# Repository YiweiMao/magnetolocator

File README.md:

# magnetolocator

Check here to see our progress:
Hackathon Force Feedback VR Glove
https://docs.google.com/document/d/1uaAP13nhqvj-tF6IxJNAysReoOo3x5oB9gJD-OO6OQ0/edit

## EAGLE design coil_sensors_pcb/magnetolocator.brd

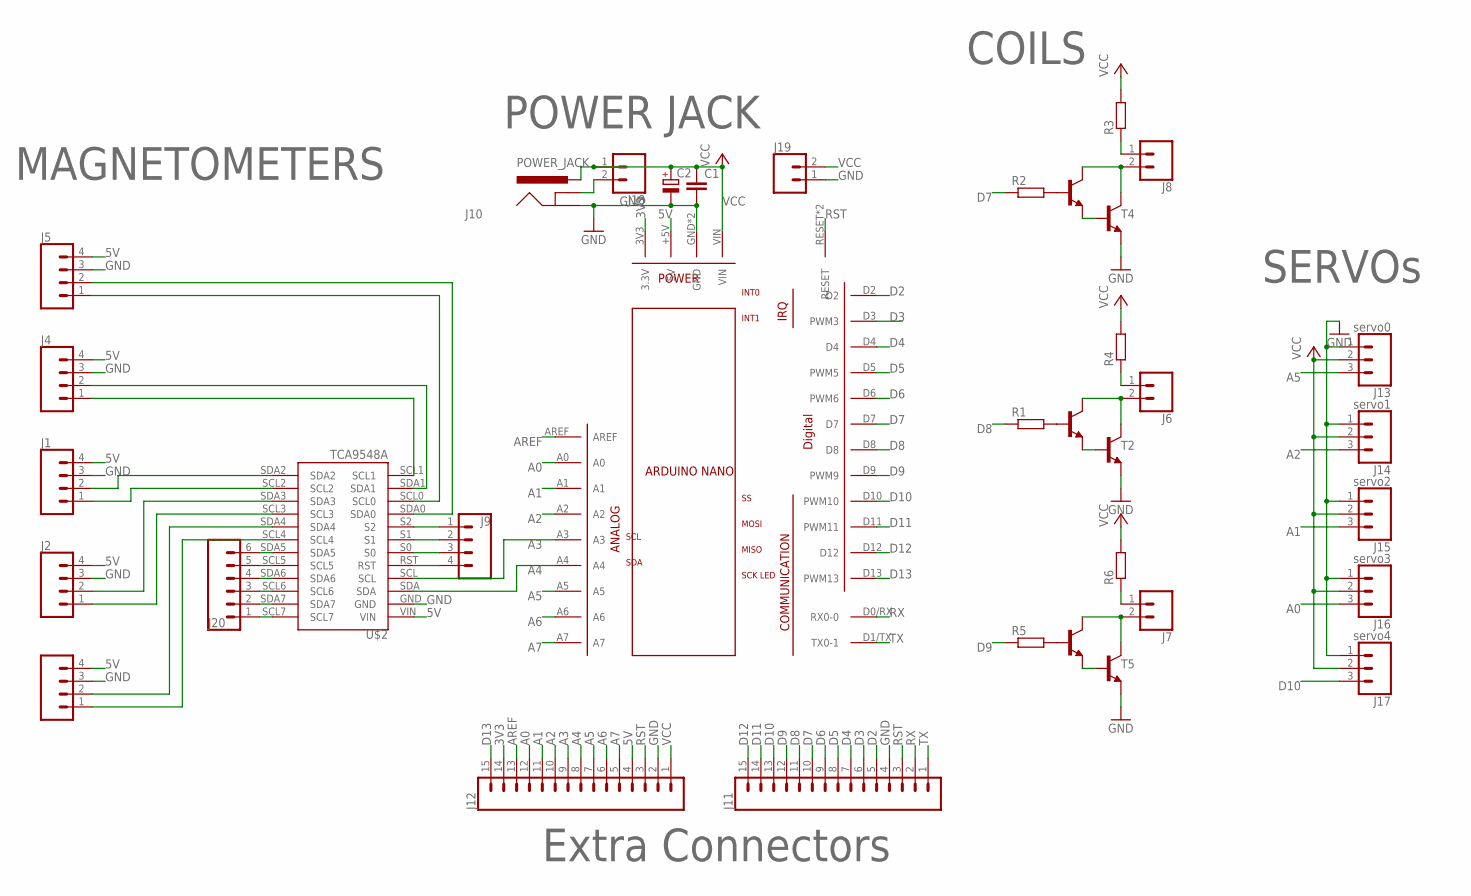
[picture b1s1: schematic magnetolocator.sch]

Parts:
C1: C-EU025-025X050; C025-025X050
C2: CPOL-EUE2.5-5; E2,5-5
J1, J2, J3, J4, J5, J9: CONN_04PTH; 1X04
J6, J7, J8, J18, J19: CONN_02; 1X02
J10: POWER_JACK; POWER_JACK_PTH
J11, J12: CONN_15; 1X15
J13: servo0; 1X03
J14: servo1; 1X03
J15: servo2; 1X03
J16: servo3; 1X03
J17: servo4; 1X03
J20: CONN_06NO_SILK_FEMALE_PTH; 1X06_NO_SILK
R1, R2, R3, R4, R5, R6: R-EU_0207/2V; 0207/2V
T1, T2, T3, T4, T5, T6: 2N2222-NPN-TO92-EBC; TO92-EBC
U$1: BOARD_ARDUINO-NANO; BOARD_ARDUINO_NANO
U$2: TCA9548A

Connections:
3V3: J12.14, U$1.3V3 (3.3V)
5V: J1.4, J2.4, J3.4, J4.4, J5.4, J12.4, U$1.+5V (5V), U$2.VIN
A0: J12.12, J16.3, U$1.A0
A1: J12.11, J15.3, U$1.A1
A2: J12.10, J14.3, U$1.A2
A3: J12.9, U$1.A3, U$2.SCL
A4: J12.8, U$1.A4, U$2.SDA
A5: J12.7, J13.3, U$1.A5
A6: J12.6, U$1.A6
A7: J12.5, U$1.A7
AREF: J12.13, U$1.AREF
D2: J11.5, U$1.D2
D3: J11.6, U$1.D3 (PWM3)
D4: J11.7, U$1.D4
D5: J11.8, U$1.D5 (PWM5)
D6: J11.9, U$1.D6 (PWM6)
D7: J11.10, R2.1, U$1.D7
D8: J11.11, R1.1, U$1.D8
D9: J11.12, R5.1, U$1.D9 (PWM9)
D10: J11.13, J17.3, U$1.D10 (PWM10)
D11: J11.14, U$1.D11 (PWM11)
D12: J11.15, U$1.D12
D13: J12.15, U$1.D13 (PWM13)
GND: C1.2, C2.-, J1.3, J2.3, J3.3, J4.3, J5.3, J10.GND, J11.4, J12.2, J13.1, J14.1, J15.1, J16.1, J17.1, J19.1, T2.E, T4.E, T5.E, U$1.GND, U$1.GND1 (GND), U$2.GND
unnamed: R2.2, T1.B
unnamed: R1.2, T3.B
unnamed: J3.1, U$2.SCL4
unnamed: J3.2, U$2.SDA4
unnamed: J8.1, R3.1
unnamed: J10.GNDBREAK, J18.2
unnamed: T1.E, T4.B
unnamed: J8.2, T1.C, T4.C
unnamed: J2.1, U$2.SCL3
unnamed: J2.2, U$2.SDA3
unnamed: J6.1, R4.1
unnamed: T2.B, T3.E
unnamed: J1.1, U$2.SCL2
unnamed: J1.2, U$2.SDA2
unnamed: J6.2, T2.C, T3.C
unnamed: R5.2, T6.B
unnamed: J4.1, U$2.SCL1
unnamed: J4.2, U$2.SDA1
unnamed: J7.1, R6.1
unnamed: T5.B, T6.E
unnamed: J5.1, U$2.SCL0
unnamed: J5.2, U$2.SDA0
unnamed: J7.2, T5.C, T6.C
unnamed: J9.1, U$2.S2
unnamed: J9.2, U$2.S1
unnamed: J9.3, U$2.S0
unnamed: J9.4, U$2.RST
unnamed: J20.1, U$2.SCL7
unnamed: J20.2, U$2.SDA7
unnamed: J20.3, U$2.SCL6
unnamed: J20.4, U$2.SDA6
unnamed: J20.5, U$2.SCL5
unnamed: J20.6, U$2.SDA5
RST: J11.3, J12.3, U$1.RESET, U$1.RESET1 (RESET)
RX: J11.2, U$1.D0/RX (RX0-0)
TX: J11.1, U$1.D1/TX (TX0-1)
VCC: C1.1, C2.+, J10.PWR, J12.1, J13.2, J14.2, J15.2, J16.2, J17.2, J18.1, J19.2, R3.2, R4.2, R6.2, U$1.VIN

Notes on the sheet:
MAGNETOMETERS
POWER JACK
COILS
SERVOs
Extra Connectors

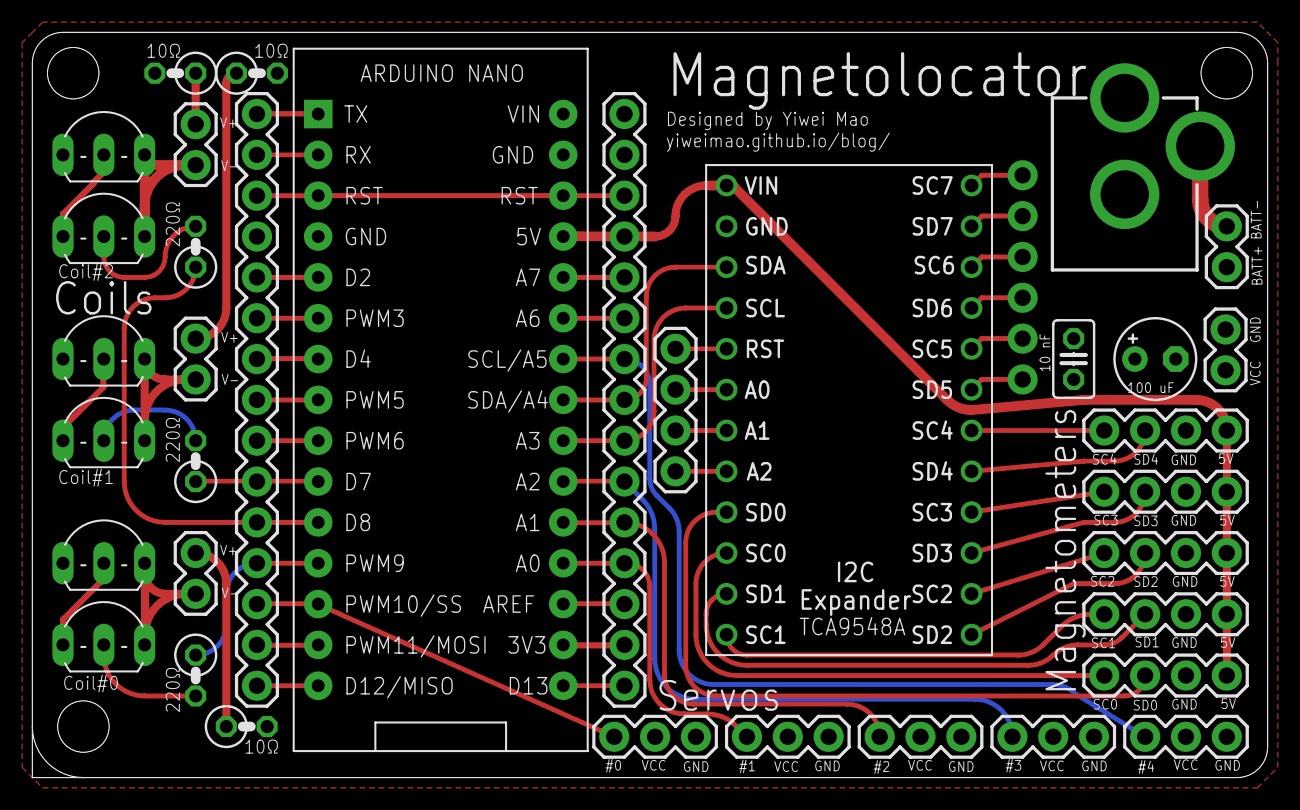
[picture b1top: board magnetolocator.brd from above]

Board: 2 copper layers, 76.8 x 46.4 mm, 36 parts (0 on the bottom side), 61 nets.

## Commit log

2020-01-25 got someone else's curve fit library compiling
2020-01-25 updated README with gDoc link.
2020-01-25 Basic mag read outs
2020-01-25 added notebook FFT code
2020-01-25 Reading serial
2020-01-25 added custom magnetometer cpp file for high performace
2020-01-25 reports all mag info on one line
2020-01-26 frequency interrupts added
2020-02-29 added state to struct becuase Jack was angry at me
2020-02-29 electromag and magnetometer in classes
2020-02-29 added frequency rates for all electro mags
2020-02-29 refactored structure
2020-02-29 Changed folders
2020-02-29 Made code nice, still don't know if it compiles
2020-02-29 Compiles now!!!
2020-02-29 Got readings and coils working but dies soon yeet
2020-03-02 pcbs for yw
2020-04-23 added pcb files
2020-05-07 updated pcb

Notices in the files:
parts and their libraries:
SparkFun-Connectors: Licensing: Creative Commons ShareAlike 4.0 International - https://creativecommons.org/licenses/by-sa/4.0
